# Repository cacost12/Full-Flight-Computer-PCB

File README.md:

<h1>Full Feature Flight Computer</h1>

<p><b>Current PCB Revision:</b> 1.0</p>
<p><b>PCB Part Number:</b> A0002</p>

<p>
The full feature flight computer supports the full range of amateur rocketry recovery and launch configurations 
such as dual-deploy parachute recovery, staging, IMU and barometric pressure sensor data logging, and redundant
parachute ejection. In addition to all the functionality of the base flight computer model, the full feature 
board includes two IMUs for low and high G data collection, and two auxiliary ignition ports for use with staging
ignition and/or redunant parachute ejection charges. 
 </p>

<b>Working Directory Structure:</b>
 
 <p>
cad: 3d models

doc: documentation

img: images of circuit/footprints for github display 
    
lib: libraries for schematic symbols and footprints
 
production: files needed for pcb fabrication, e.g. gerbers, profile, drill fi    le
 
sim: simulation files 
   
src: source design files, e.g. schematic and board files
 </p>

<h2>3D Model: </h2>

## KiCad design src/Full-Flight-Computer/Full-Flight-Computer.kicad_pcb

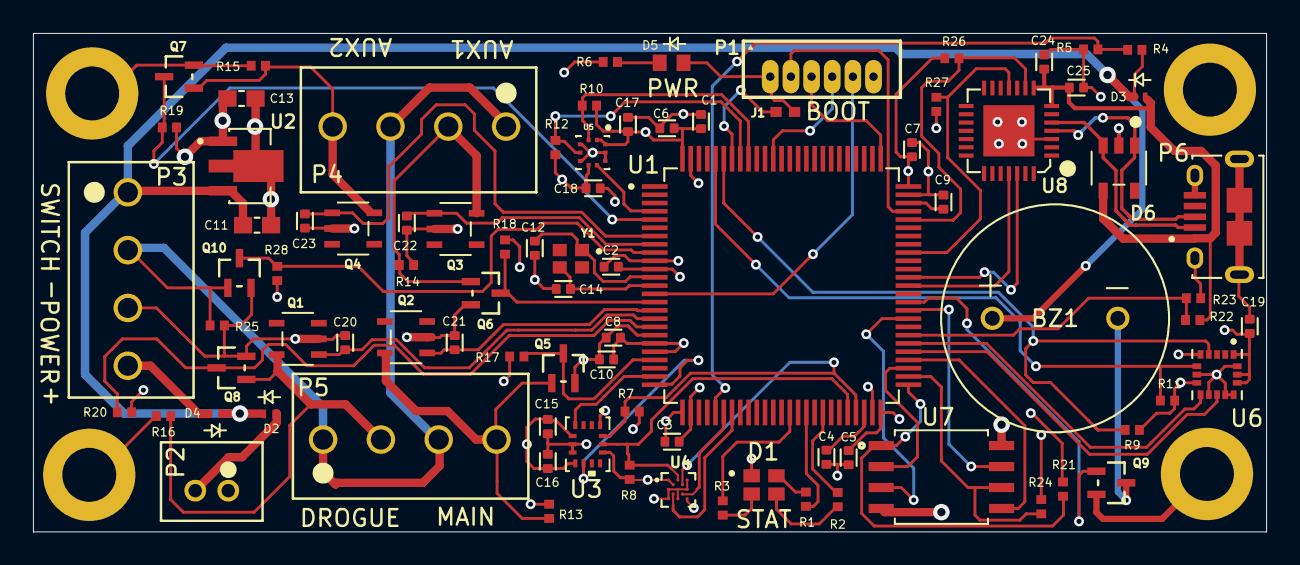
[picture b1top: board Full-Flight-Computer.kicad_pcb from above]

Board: 4 copper layers, 74.7 x 30.2 mm, 90 parts (0 on the bottom side), 65 nets.

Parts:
BZ1: AT-1438-TWT-R
C1: 4.7uF; CAP_0402
C2, C3, C5, C6, C7, C8, C15, C16, C17, C18, C19, C25: 0.1uF; CAP_0402
C4, C9: 2.2uF; CAP_0402
C10, C20, C21, C22, C23, C24: 1uF; CAP_0402
C11, C13: 1uF; CAP_0603
C12, C14: 8pF; CAP_0402
D1: CLMVC-FKA-CL1D1L71BB7C3C3
D2, D3, D4: PMEG3010AESBYL
D5: LTST-C191KGKT
D6: SP0504BAHTG
H1, H2: Mounting-Hole-4-40; MountingHole_4-40
H3, H4: Mounting-Hole; MountingHole_4-40
J1: Jumper_NO; Jumper-NO
P1: 0530470610; 53047-0610
P2: B2B-PH-K-SLFSN_JST
P3, P5: 1984659; 1546551-4
P4: 1546551-4
P6: USB; 10118194-0001LF
Q1, Q2, Q3, Q4: QS5U17TR
Q5, Q6, Q7, Q8, Q9, Q10: 2N7002W-7-F
R1, R2: 82; RES_0402
R3, R6: 240; RES_0402
R4: 39k; RES_0402
R5, R7, R8, R9, R11, R17, R18, R19, R20, R21, R24, R27, R28: 10k; RES_0402
R10, R12, R26: 4.7k; RES_0402
R13, R14, R15, R16, R22, R25: 100k; RES_0402
R23: 200k; RES_0402
U1: STM32H750VBTx; STM32H750VBT6
U2: AP7370-33Y-13
U3: BMI323
U4: BMM150
U5: BMP390
U6: H3LIS100DLTR
U7: SST25VF040B-50-4I-S2AE-T
U8: CP2102-GMR(QFN28); CP2012-GMR
Y1: ECS-240-18-33-JGN-TR; ECS-240-12-37B-CKY-TR

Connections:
3.3V: C1.1, C2.1, C3.1, C5.1, C6.1, C7.1, C8.1, C10.1, C13.1, C15.1, C16.1, C17.1, C18.1, C19.1, D1.1, D5.2, J1.1 (A), P1.1, R7.2, R8.2, R9.2, R10.2, R11.2, R12.2, R17.2, R18.2, R19.2, R20.2, R21.2, R26.1, R28.2, U1.11 (VDD), U1.20 (VREF+), U1.21 (VDDA), U1.27 (VDD), U1.50 (VDD), U1.75 (VDD), U1.100 (VDD), U2.1 (VOUT), U3.5 (VDDIO), U3.8 (VDD), U3.12 (CSB), U4.A1 (PS), U4.B2 (VDDIO), U4.E5 (VDD), U5.1 (VDDIO), U5.6 (CSB), U5.10 (VDD), U6.1 (VDD_IO), U6.8 (CS), U6.14 (VDD), U6.15 (VDD), U7.8 (VDD)
5V: C24.1, C25.1, D3.A, D6.4, P6.1 (VCC), R22.2, U8.7 (REGIN), U8.8 (VBUS)
/Peripherals/D+: D6.1, P6.3 (D+), U8.4 (D+)
/Peripherals/D-: D6.3, P6.2 (D-), U8.5 (D-)
AUX1: C22.1, Q3.1 (G), U1.8 (PC14)
AUX2: C23.1, Q4.1 (G), U1.7 (PC13)
BEEP: Q9.1 (G), U1.61 (PD14)
BOOT: J1.2 (B), U1.94 (BOOT0)
BP_INT: U1.4 (PE5), U5.7 (INT)
BP_SCL: R10.1, U1.92 (PB6), U5.2 (SCK)
BP_SDA: R12.1, U1.93 (PB7), U5.4 (SDI)
CAP1: C4.1, U1.48 (VCAP1)
CAP2: C9.1, U1.73 (VCAP2)
DROGUE: C20.1, Q1.1 (G), U1.17 (PC2_C)
Earth: C1.2, C2.2, C3.2, C4.2, C5.2, C6.2, C7.2, C8.2, C9.2, C10.2, C11.2, C12.2, C13.2, C14.2, C15.2, C16.2, C17.2, C18.2, C19.2, C20.2, C21.2, C22.2, C23.2, C24.2, C25.2, D6.2, H1.1, H2.1, H3.1, H4.1, P1.6, P2.1 (5), P3.3 (5), P6.5 (GND), P6.S1 (SHIELD), P6.S2 (SHIELD), Q1.2 (S), Q2.2 (S), Q3.2 (S), Q4.2 (S), Q5.2 (S), Q6.2 (S), Q7.2 (S), Q8.2 (S), Q9.2 (S), Q10.2 (S), R5.1, R6.1, R13.1, R14.1, R15.1, R16.1, R23.1, R24.1, R25.1, R27.1, U1.10 (VSS), U1.19 (VSSA), U1.26 (VSS), U1.49 (VSS), U1.74 (VSS), U1.99 (VSS), U2.2 (GND), U3.1 (SDO), U3.6 (GNDIO), U3.7 (GND), U4.A5 (CSB), U4.C1 (SDO), U4.C5 (GND), U4.E1 (GND), U4.E3 (GND), U5.3 (VSS), U5.5 (SDO), U5.8 (VSS), U5.9 (VSS), U6.5 (GND), U6.7 (SDO/SA0), U6.10 (GND), U6.12 (GND), U6.13 (GND), U6.16 (GND), U7.4 (VSS), U8.3 (GND), U8.29 (PAD)
FLASH_MISO: U1.53 (PB14), U7.2 (SO)
FLASH_MOSI: U1.54 (PB15), U7.5 (SI)
FLASH_SCK: R24.2, U1.52 (PB13), U7.6 (SCK)
HG_ACC_INT1: U1.55 (PD8), U6.11 (INT1)
HG_ACC_INT2: U1.56 (PD9), U6.9 (INT2)
HG_ACC_SCL: R9.1, U1.95 (PB8), U6.4 (SCL/SPC)
HG_ACC_SDA: R11.1, U1.96 (PB9), U6.6 (SDA/SDI/SDO)
IMU_INT1: U1.24 (PA2), U3.4 (INT1)
IMU_INT2: U1.25 (PA3), U3.9 (INT2)
MAG_DRDY: U1.31 (PA7), U4.D4 (DRDY)
MAG_INT: U1.32 (PC4), U4.D2 (INT)
MAIN: C21.1, Q2.1 (G), U1.16 (PC1)
NRST: P1.5, U1.14 (NRST)
unnamed: BZ1.2 (+), Q9.3 (D)
unnamed: D1.2, R1.2
unnamed: D1.3, R2.2
unnamed: D1.4, R3.2
unnamed: D5.1, R6.2
unnamed: D2.A, P2.2 (6)
unnamed: D4.A, P3.4 (6)
unnamed: P4.2 (6), Q3.5 (D), Q6.1 (G), R14.2
unnamed: P4.4 (6), Q4.5 (D), Q7.1 (G), R15.2
unnamed: P5.2 (6), Q1.5 (D), Q8.1 (G), R16.2
unnamed: P5.4 (6), Q2.5 (D), Q5.1 (G), R13.2
OSC_IN: C12.1, U1.12 (PH0), Y1.1
OSC_OUT: C14.1, U1.13 (PH1), Y1.3
RX_USB: U1.63 (PC6), U8.25 (RXD)
SCL: R8.1, U1.46 (PB10), U3.13 (SCX), U4.A3 (SCK)
SDA: R7.1, U1.47 (PB11), U3.14 (SDX), U4.B4 (SDI)
STATUS_B: R1.1, U1.41 (PE11)
STATUS_G: R2.1, U1.43 (PE13)
STATUS_R: R3.1, U1.39 (PE9)
SWCLK: P1.3, U1.76 (PA14)
SWDIO: P1.2, U1.72 (PA13)
SWO: P1.4, U1.89 (PB3)
TX_USB: U1.64 (PC7), U8.26 (TXD)
USB_DETECT: R22.1, R23.2, U1.57 (PD10)
VBAT_SENSE: R4.2, R5.2, U1.30 (PA6)
VIN: BZ1.1 (-), C11.1, D2.C, D3.C, D4.C, P3.1 (5), R4.1, U2.3 (VIN)
VIN_SW: P3.2 (6), P4.1 (5), P4.3 (5), P5.1 (5), P5.3 (5), Q10.1 (G), R25.2
~AUX1_CONT: Q6.3 (D), R18.1, U1.15 (PC0)
~AUX2_CONT: Q7.3 (D), R19.1, U1.5 (PE6)
~DROGUE_CONT: Q8.3 (D), R20.1, U1.18 (PC3_C)
~FLASH_HOLD: U1.60 (PD13), U7.7 (*HOLD)
~FLASH_SS: R21.1, U1.51 (PB12), U7.1 (*CE)
~FLASH_WP: U1.59 (PD12), U7.3 (*WP)
~MAIN_CONT: Q5.3 (D), R17.1, U1.22 (PA0)
~SWITCH: Q10.3 (D), R28.1, U1.9 (PC15)
~USB_RST: R26.2, U1.71 (PA12), U8.9 (~RST)
~USB_SUSPEND: R27.2, U1.67 (PA8), U8.11 (~SUSPEND)

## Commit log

2023-06-11 updated README with correct project info
2023-06-11 removed old flight computer images
2023-06-11 removed old CAD files
2023-06-11 removed old schematic and gerber files
2023-06-11 renamed project file to full-flight-computer
2023-06-11 added kicad backup directories to gitignore
2023-06-11 created new footprint library
2023-06-11 created new symbol library
2023-06-11 removed extra sections from schematic
2023-06-12 fixed all schematic symbol links to link to correct lib file
2023-06-12 added auxiliary ports for staging/redundant ejection charges
2023-06-12 added high G accelerometer to lib files
2023-06-12 implemented high G accelerometer schematic
2023-06-12 redid component designators and updated BOM
2023-06-14 placed all components on test board
2023-06-15 completed initial layout
2023-06-15 resolved all DRC errors
2023-06-15 moved BP_INT signal to new MCU pin to avoid EXTI collision with IMU interrupt signal
2023-06-15 added fabrication outputs
2023-06-15 added PCB images to README
2023-07-04 add IMU prefix to IMU SDA and SCL labels
2023-08-03 generated BOM from shcematic

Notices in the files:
parts and their libraries:
Copyright 2021 Accelerated Designs. All rights reserved.
